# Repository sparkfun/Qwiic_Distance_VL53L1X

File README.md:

SparkFun Qwiic 4m Distance Sensor with VL53L1X
========================================

[*SparkFun Distance Sensor Breakout - 4 Meter, VL53L1X (Qwiic)(SEN-14722)*](https://www.sparkfun.com/products/14722)

The VL53L1X is the latest Time Of Flight (ToF) sensor to be released. It uses a VCSEL (vertical cavity surface emitting laser) to emit a class 1 IR laser and time the reflection to the target. What does all this mean? You can measure the distance to an object up to 4 meters away with millimeter resolution! That’s pretty incredible.

We’re far from done: The VL53L1X is a highly complex sensor with a multitude of options and configurations. We’ve written example sketches that allow you to read the distance, signal rate, and range status. Because ST has chosen not to release a complete datasheet we are forced to reverse engineer the interface from their example code and I2C data stream captures. If you’re into puzzles we could use your help to make the library better!

We’ve found the precision of the sensor to be 1mm but the accuracy is around +/-5mm.

SparkFun labored with love to create this code. Feel like supporting open source hardware? 
Buy a [breakout board](https://www.sparkfun.com/products/14722) from SparkFun!

Repository Contents
-------------------

* **/Documents** - Datasheet and User Manual
* **/Hardware** - Eagle design files (.brd, .sch)
* **/Production** - .brd files

Documentation
--------------
* **[Arduino Library](https://github.com/sparkfun/SparkFun_VL53L1X_Arduino_Library)** - Library for reading distance in millimeters, signal rate, status, etc.
* **[Hookup Guide](https://learn.sparkfun.com/tutorials/qwiic-distance-sensor-vl53l1x-vl53l4cd-hookup-guide)** - Basic hookup guide for the VL53L1X and VL53L4CD.

Product Versions
--------------
* **[SEN-14722](https://www.sparkfun.com/products/14722)** - SparkFun red version
* **[SPX-14667](https://www.sparkfun.com/products/14667)** - SparkX Version 

License Information
-------------------

This product is _**open source**_! 

Please review the LICENSE.md file for license information. 

If you have any questions or concerns on licensing, please contact techsupport@sparkfun.com.

Please use, reuse, and modify these files as you see fit. Please maintain attribution to SparkFun Electronics and release any derivative under the same license.

Distributed as-is; no warranty is given.

- Your friends at SparkFun.

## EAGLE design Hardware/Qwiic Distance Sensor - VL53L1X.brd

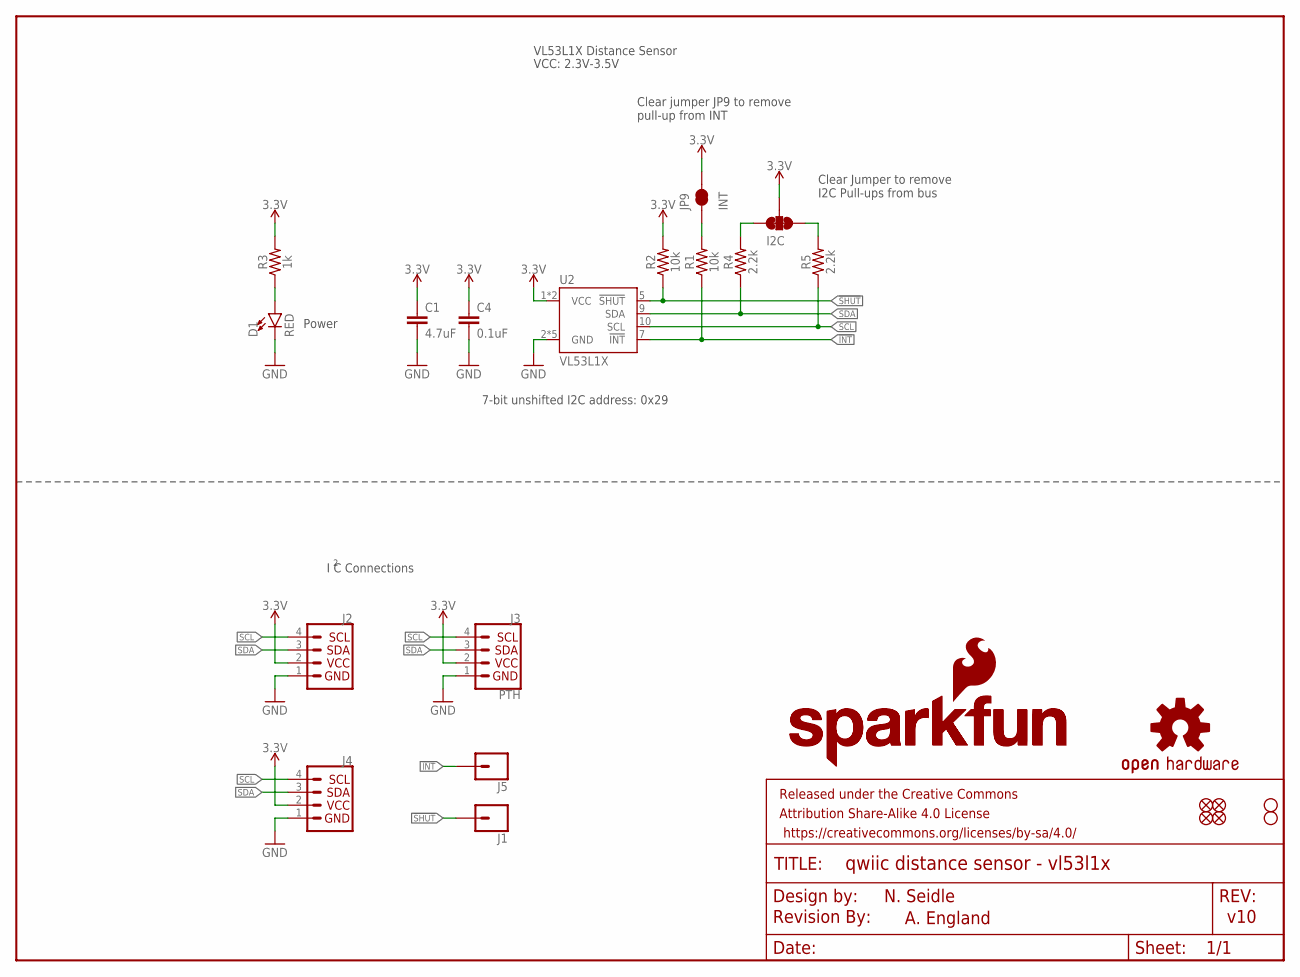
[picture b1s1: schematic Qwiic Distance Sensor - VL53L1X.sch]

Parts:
C1: 4.7uF; 0603
C4: 0.1uF; 0603
D1: RED; LED-0603
FRAME1: FRAME-LETTER; CREATIVE_COMMONS
I2C: JUMPER-SMT_3_2-NC_TRACE_SILK; SMT-JUMPER_3_2-NC_TRACE_SILK
J1, J5: CONN_01PTH_NO_SILK_YES_STOP; 1X01_NO_SILK
J2, J4: QWIIC_CONNECTORJS-1MM; 1X04_1MM_RA
J3: PTH; 1X04_NO_SILK
JP1, JP2, JP5, JP6: FIDUCIALUFIDUCIAL; MICRO-FIDUCIAL
JP3, JP4: STAND-OFF
JP9: INT; PAD-JUMPER-2-NC_BY_TRACE_YES_SILK
LOGO1: OSHW-LOGOMINI; OSHW-LOGO-MINI
LOGO2: REVISION
R1, R2: 10k; 0603
R3: 1k; 0603
R4, R5: 2.2k; 0603
U2: VL53L1X
U$1: SFE_LOGO_NAME.1_INCH; SFE_LOGO_NAME_.1
U$2: SFE_LOGO_NAME_FLAME.1_INCH; SFE_LOGO_NAME_FLAME_.1

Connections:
3.3V: C1.1, C4.1, I2C.2, J2.2, J3.2 (VCC), J4.2, JP9.2, R2.2, R3.2, U2.1 (VCC), U2.11 (VCC)
!INT: J5.1, R1.1, U2.7 (!INT)
!SHUT: J1.1, R2.1, U2.5 (!SHUT)
GND: C1.2, C4.2, D1.C, J2.1, J3.1 (GND), J4.1, U2.2 (GND), U2.3 (GND), U2.4 (GND), U2.6 (GND), U2.12 (GND)
unnamed: I2C.1, R5.2
unnamed: I2C.3, R4.2
unnamed: D1.A, R3.1
unnamed: JP9.1, R1.2
SCL: J2.4, J3.4 (SCL), J4.4, R5.1, U2.10 (SCL)
SDA: J2.3, J3.3 (SDA), J4.3, R4.1, U2.9 (SDA)

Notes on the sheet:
N. Seidle
v10
7-bit unshifted I2C address: 0x29
Clear Jumper to remove I2C Pull-ups from bus
Clear jumper JP9 to remove pull-up from INT
Power
A. England
I C Connections
VL53L1X Distance Sensor
VCC: 2.3V-3.5V

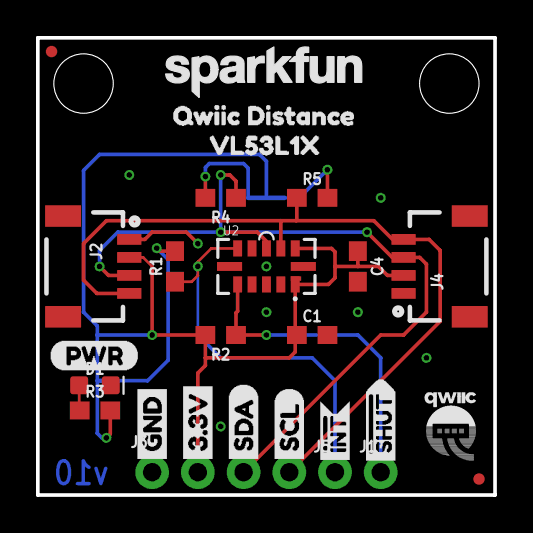
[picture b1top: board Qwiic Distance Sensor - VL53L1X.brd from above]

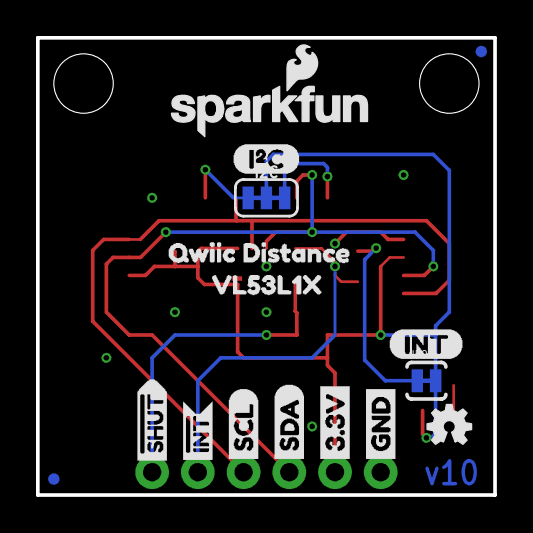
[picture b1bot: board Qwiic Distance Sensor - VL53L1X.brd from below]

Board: 2 copper layers, 25.4 x 25.4 mm, 47 parts (16 on the bottom side), 10 nets.

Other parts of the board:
U$3, U$22: GND1
U$4, U$21: 3#3V2
U$5, U$27: SDA8
U$6, U$26: SCL9
U$7, U$14: INT#-[<
U$8, U$9: #SHUT15
U$10: (PWR)
U$11: (I_SUPER2_C)
U$12: (INT)
U$13: QWIIC-LOGO-SMALL
U$15, U$19: QWIIC_DISTANCE0
U$16, U$20: VL53L1X1

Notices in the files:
parts and their libraries:
SparkFun-Resistors: Licensing: Creative Commons ShareAlike 4.0 International - https://creativecommons.org/licenses/by-sa/4.0
SparkFun-Aesthetics: Released under the Creative Commons Attribution Share-Alike 4.0 License
SparkFun-Aesthetics: https://creativecommons.org/licenses/by-sa/4.0
